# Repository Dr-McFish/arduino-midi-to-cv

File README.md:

# arduino-midi-to-cv
This arduino project accsepts MIDI input and translates it into various control voltages for a synthesiser.

## Features

 * 0 to 5 volt v/octave output, with 0V corresponding to MIDI note 36 (C2).
 * Monophonic, highest note priority
 * Gate Output
 
### Work in progress (planned features):

 * Pitch bend support (on the v/octave output)
 * Mod wheel output
 * Velocity output
 * OLED screen with options menu
 * Note priority option
 * Gate retrigger/legato option

## Installation requirements

 * if one desires this to work over usb, then flashing the [mocoLUFA](https://github.com/kuwatay/mocolufa) firware to the arduino is required. I personaly found this [tutorial](https://youtu.be/-bCz2I9SMAA) helpfull. Otherwise use a 5 pin MIDI connector circuit(not shown).
 * Upload with arduino IDE or comand line utility

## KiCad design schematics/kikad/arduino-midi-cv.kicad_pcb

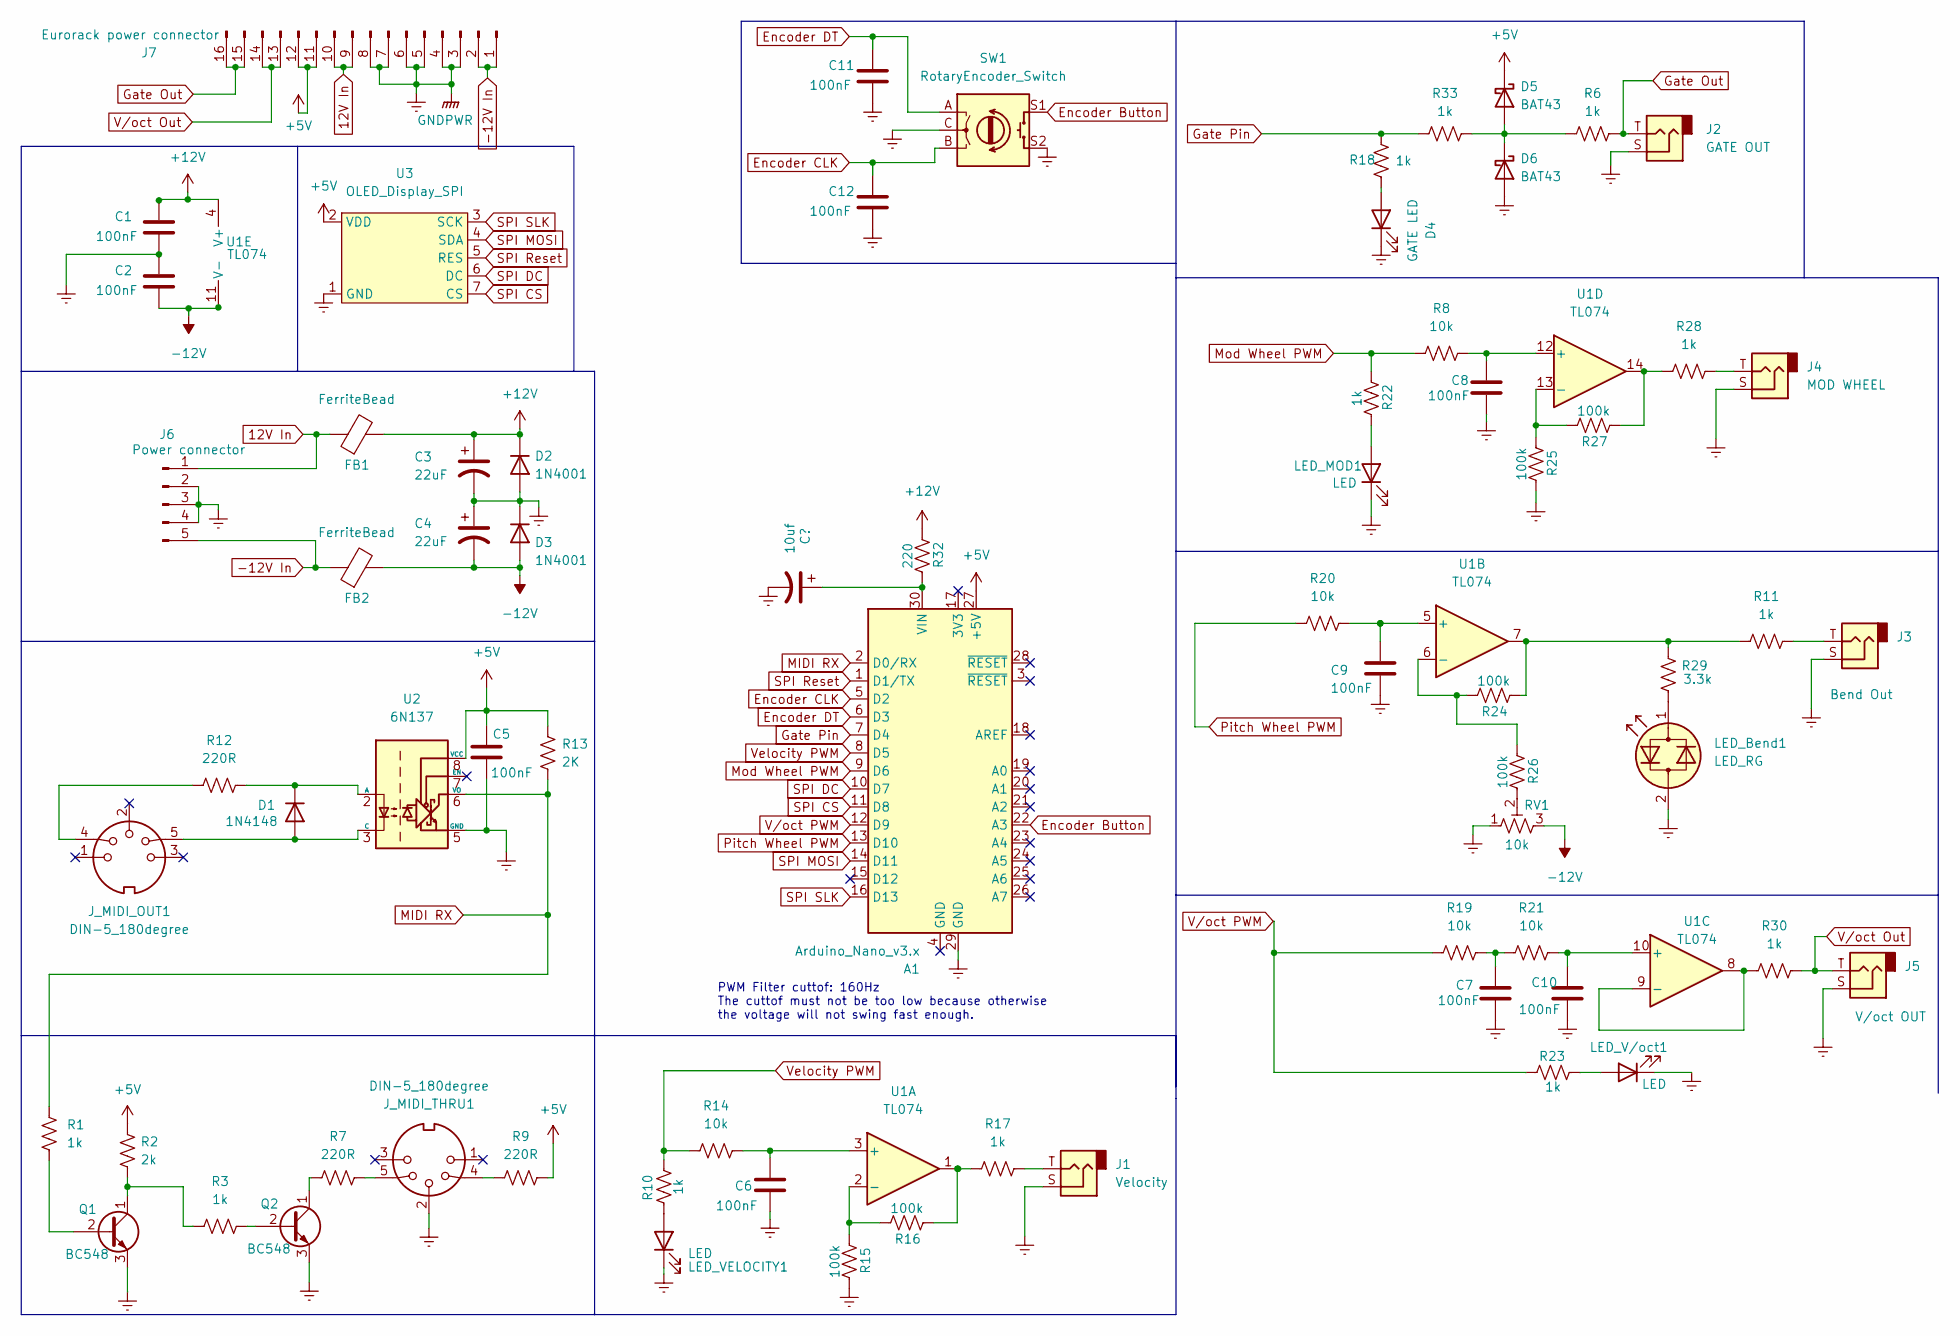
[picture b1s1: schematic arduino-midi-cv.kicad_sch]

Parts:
A1: Arduino_Nano_v3.x; Arduino_Nano
C1, C2, C5, C6, C7, C8, C9, C10, C11, C12: 100nF; C_Disc_D3.0mm_W1.6mm_P2.50mm
C3, C4: 22uF; CP_Radial_D5.0mm_P2.50mm
D1: 1N4148; D_DO-35_SOD27_P2.54mm_Vertical_AnodeUp
D2, D3: 1N4001; D_DO-41_SOD81_P12.70mm_Horizontal
D4: GATE LED; LED_D5.0mm
D5, D6: BAT43; D_DO-35_SOD27_P7.62mm_Horizontal
FB1, FB2: FerriteBead; R_Axial_DIN0207_L6.3mm_D2.5mm_P10.16mm_Horizontal
J1: Velocity; Jack breakcout cables
J2: GATE OUT; Jack breakcout cables
J3: Bend Out; Jack breakcout cables
J4: MOD WHEEL; Jack breakcout cables
J5: V/oct OUT; Jack breakcout cables
J6: Power connector; JST_XH_B5B-XH-A_1x05_P2.50mm_Vertical
J7: Eurorack power connector; IDC-Header_2x08_P2.54mm_Vertical
J_MIDI_OUT1: DIN-5_180degree; SIP-2
J_MIDI_THRU1: DIN-5_180degree; SIP-2
LED_Bend1: LED_RG; LED_D5.0mm
LED_MOD1: LED; LED_D5.0mm
LED_V/oct1: LED; LED_D5.0mm
LED_VELOCITY1: LED; LED_D5.0mm
Q1, Q2: BC548; TO-92_Inline
R1, R3, R6, R10, R11, R17, R18, R22, R23, R28, R30, R33: 1k; R_Axial_DIN0207_L6.3mm_D2.5mm_P10.16mm_Horizontal
R2: 2k; R_Axial_DIN0207_L6.3mm_D2.5mm_P10.16mm_Horizontal
R7, R9: 220R; R_Axial_DIN0207_L6.3mm_D2.5mm_P10.16mm_Horizontal
R8, R14, R19, R20, R21: 10k; R_Axial_DIN0207_L6.3mm_D2.5mm_P10.16mm_Horizontal
R12: 220R; R_Axial_DIN0207_L6.3mm_D2.5mm_P2.54mm_Vertical
R13: 2K; R_Axial_DIN0207_L6.3mm_D2.5mm_P7.62mm_Horizontal
R15, R26: 100k; R_Axial_DIN0207_L6.3mm_D2.5mm_P10.16mm_Horizontal
R16, R24, R25, R27: 100k; R_Axial_DIN0207_L6.3mm_D2.5mm_P2.54mm_Vertical
R29: 3.3k; R_Axial_DIN0207_L6.3mm_D2.5mm_P10.16mm_Horizontal
R32: 220; R_0805_2012Metric_Pad1.20x1.40mm_HandSolder
RV1: 10k; Potentiometer_Bourns_3296W_Vertical
SW1: RotaryEncoder_Switch; RotaryEncoder_Alps_EC11E-Switch_Vertical_H20mm
U1: TL074; DIP-14_W7.62mm_Socket
U2: 6N137; DIP-8_W7.62mm
U3: OLED_Display_SPI; SPI Oled dislay SH1106

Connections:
12V In: FB1.1, J6.1, J7.9, J7.10
+5V: A1.27 (+5V), C5.1, D5.1 (K), J7.11, J7.12, R2.2, R9.1, R13.2, U2.8 (VCC), U3.2 (VDD)
+12V: C1.1, C3.1, D2.1 (K), FB1.2, R32.2, U1.4 (V+)
-12V: C2.2, C4.2, D3.2 (A), FB2.2, RV1.3, U1.11 (V-)
-12V In: FB2.1, J6.5, J7.1, J7.2
Earth: A1.29 (GND), C1.2, C2.1, C3.2, C4.1, C5.2, C6.2, C7.2, C8.2, C9.2, C10.2, C11.2, C12.2, D2.2 (A), D3.1 (K), D4.1 (K), D6.2 (A), J1.S, J2.S, J3.S, J4.S, J5.S, J6.2, J6.3, J6.4, J7.3, J7.4, J7.5, J7.6, J7.7, J7.8, J_MIDI_THRU1.2, LED_Bend1.2 (AK), LED_MOD1.1 (K), LED_V/oct1.1 (K), LED_VELOCITY1.1 (K), Q1.3 (E), Q2.3 (E), R15.1, R25.1, RV1.1, SW1.C, SW1.S2, U2.5 (GND), U3.1 (GND)
Encoder Button: A1.22 (A3), SW1.S1
Encoder CLK: A1.5 (D2), C12.1, SW1.B
Encoder DT: A1.6 (D3), C11.1, SW1.A
Gate Out: J2.T, J7.15, J7.16, R6.2
Gate Pin: A1.7 (D4), R18.1, R33.1
MIDI RX: A1.2 (D0/RX), R1.2, R13.1, U2.6 (VO)
Mod Wheel PWM: A1.9 (D6), R8.1, R22.2
unnamed: A1.30 (VIN), R32.1
unnamed: C6.1, R14.2, U1.3 (+)
unnamed: C7.1, R19.2, R21.1
unnamed: C8.1, R8.2, U1.12 (+)
unnamed: C9.1, R20.2, U1.5 (+)
unnamed: C10.1, R21.2, U1.10 (+)
unnamed: D1.1 (K), R12.2, U2.2 (A)
unnamed: D1.2 (A), J_MIDI_OUT1.5, U2.3 (C)
unnamed: D4.2 (A), R18.2
unnamed: D5.2 (A), D6.1 (K), R6.1, R33.2
unnamed: J1.T, R17.2
unnamed: J3.T, R11.2
unnamed: J4.T, R28.2
unnamed: J_MIDI_OUT1.4, R12.1
unnamed: J_MIDI_THRU1.4, R9.2
unnamed: J_MIDI_THRU1.5, R7.1
unnamed: LED_Bend1.1 (KA), R29.2
unnamed: LED_MOD1.2 (A), R22.1
unnamed: LED_V/oct1.2 (A), R23.1
unnamed: LED_VELOCITY1.2 (A), R10.2
unnamed: Q1.1 (C), R2.1, R3.2
unnamed: Q1.2 (B), R1.1
unnamed: Q2.1 (C), R7.2
unnamed: Q2.2 (B), R3.1
unnamed: R11.1, R24.2, R29.1, U1.7
unnamed: R15.2, R16.1, U1.2 (-)
unnamed: R16.2, R17.1, U1.1
unnamed: R24.1, R26.2, U1.6 (-)
unnamed: R25.2, R27.1, U1.13 (-)
unnamed: R26.1, RV1.2
unnamed: R27.2, R28.1, U1.14
unnamed: R30.1, U1.8, U1.9 (-)
Pitch Wheel PWM: A1.13 (D10), R20.1
SPI CS: A1.11 (D8), U3.7 (CS)
SPI DC: A1.10 (D7), U3.6 (DC)
SPI MOSI: A1.14 (D11), U3.4 (SDA)
SPI Reset: A1.1 (D1/TX), U3.5 (RES)
SPI SLK: A1.16 (D13), U3.3 (SCK)
Velocity PWM: A1.8 (D5), R10.1, R14.1
V/oct Out: J5.T, J7.13, J7.14, R30.2
V/oct PWM: A1.12 (D9), R19.1, R23.2

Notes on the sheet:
PWM Filter cuttof: 160Hz The cuttof must not be too low because otherwise the voltage will not swing fast enough.

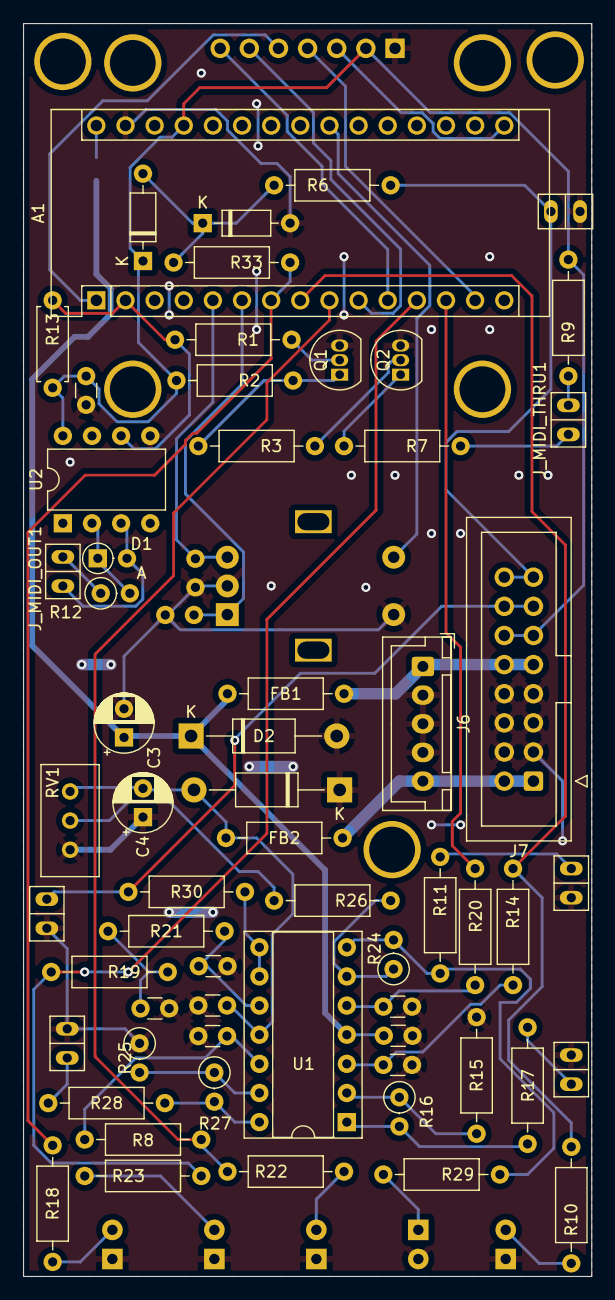
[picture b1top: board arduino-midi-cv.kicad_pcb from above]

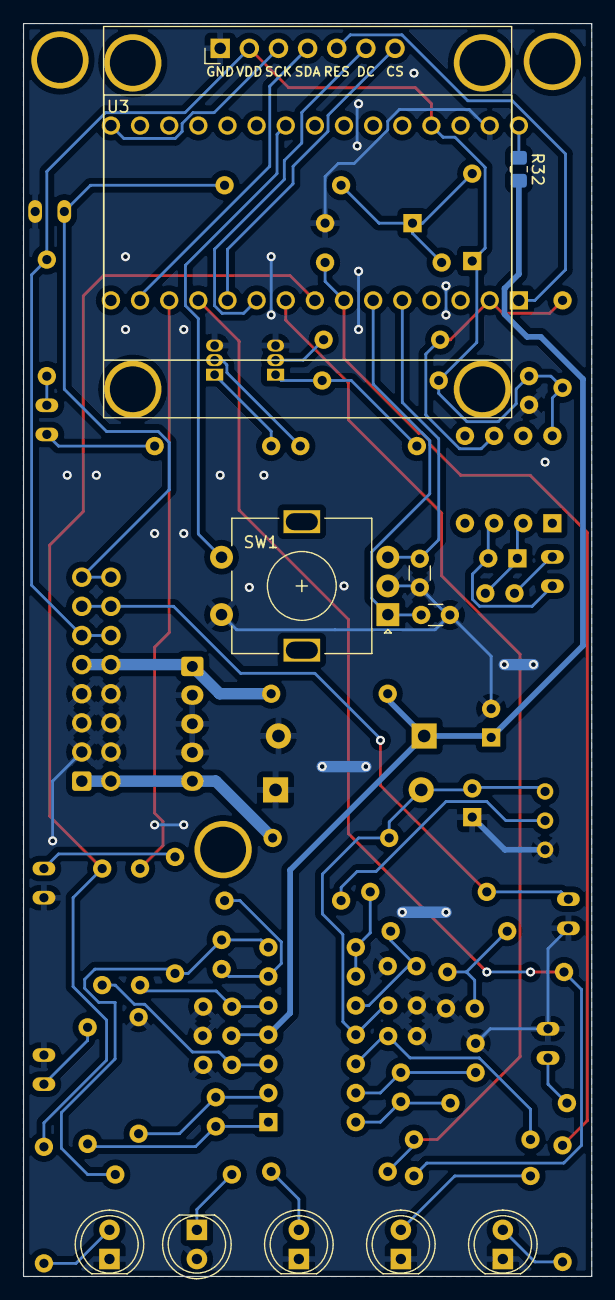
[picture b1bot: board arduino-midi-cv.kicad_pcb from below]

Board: 2 copper layers, 49.5 x 109.2 mm, 71 parts (10 on the bottom side), 54 nets.

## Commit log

2022-07-20 Add basic noteOn and noteOff support. PROTOTYPE
2022-07-20 add kikad schematic
2022-07-21 Fill out README
2022-07-21 Fix schematic pdf
2022-07-21 Upgrade v/oct to the 10 bit timer
2022-07-21 Add velocity support, add mod wheel support,
2022-07-21 Add midi CC 123: All notes (on/off)
2022-07-21 Add pitchbend
2022-07-21 Add bool_array, memory eficient data sturcture
2022-08-24 Update schematics
2022-08-24 Add .gitignore
2022-08-24 Progress on bool data structure
2022-08-25 Redraw schematics to be more butiful
2022-08-25 Add midi CC defines Add Pitch bend PWM on pin D9 Replace digitalWrite() with port manipulation for speed
2022-08-28 Recajigger the pins
2022-08-28 Start PCB
2022-08-29 Refactor code
2022-08-29 Add encoder
2022-08-29 Refactor display code into a different file
2022-08-29 Refactor loop function into several subrutines
2022-08-30 Add setting struct
2022-08-30 implement Bool Array
2022-08-30 Add Bool Array and Fix Bool Array
2022-08-31 Add settings menue ui prototype
2022-08-31 Add working menue first page prototype this code is to be reworked to make it more scalable and less terrible basicly
2022-09-01 Refactor settings code to be more modular
2022-09-01 Separate editing settings and displaying setting into separate functions
2022-09-01 Add multi page support for settings menu. Finish settings menu
2022-10-28 Add encoder button debounce
2023-07-19 There has been some work done, a long time a go I have no idea what
2023-07-20 Settup VSCode env
2023-07-20 Fix type
2023-07-20 Add DAC to shematic (untested)
2023-07-25 Change indentation to tabs. To HELL with spaces!
2023-07-27 Note priory fixes and general refactoring
2023-07-27 update schematic with new design
